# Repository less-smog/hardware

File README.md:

# IMPORTANT NOTE

The current revision (rev2) is undergoing tests - it's best to wait until the hardware has been well-tested before ordering PCBs and such.

# Open Hardware Air Pollution sensor

## housing
KRADEX Z56JPH housing is selected. Drawings and  3D models are available at [manufacturers site](https://www.kradex.com.pl/shop?product=z56).

## 3D model
Models from KiCad 4.0.7 release are used where available. Other models are in \lib\packages3d\ directory. You must copy them to KiCad KISYS3DMOD directory (i.e. C:\Program Files\KiCad\share\kicad\modules\packages3d on Windows). These models are:

* ESP-12E by [Jerry Dunmire (jdunmire)](https://github.com/jdunmire/kicad-ESP8266) (under Creative Commons Attribution-ShareAlike 4.0 International License)
* Molex 530470810, 530480810, 1050170001 by [Molex](https://www.molex.com/)
* MicroswitchSmd_4.3 by [Würth Elektronik](http://katalog.we-online.com/en/em/TASV_6X6_SMD?sid=3e9e02d6c0)
* Other are custom made

## LICENSE

This design has been released under the CERN Open Hardware Licence v1.2. We require that you notify us when you undertake either mass-production
of this design, or incorporate this design into an existing product, by e-mailing us at product@less-smog.org

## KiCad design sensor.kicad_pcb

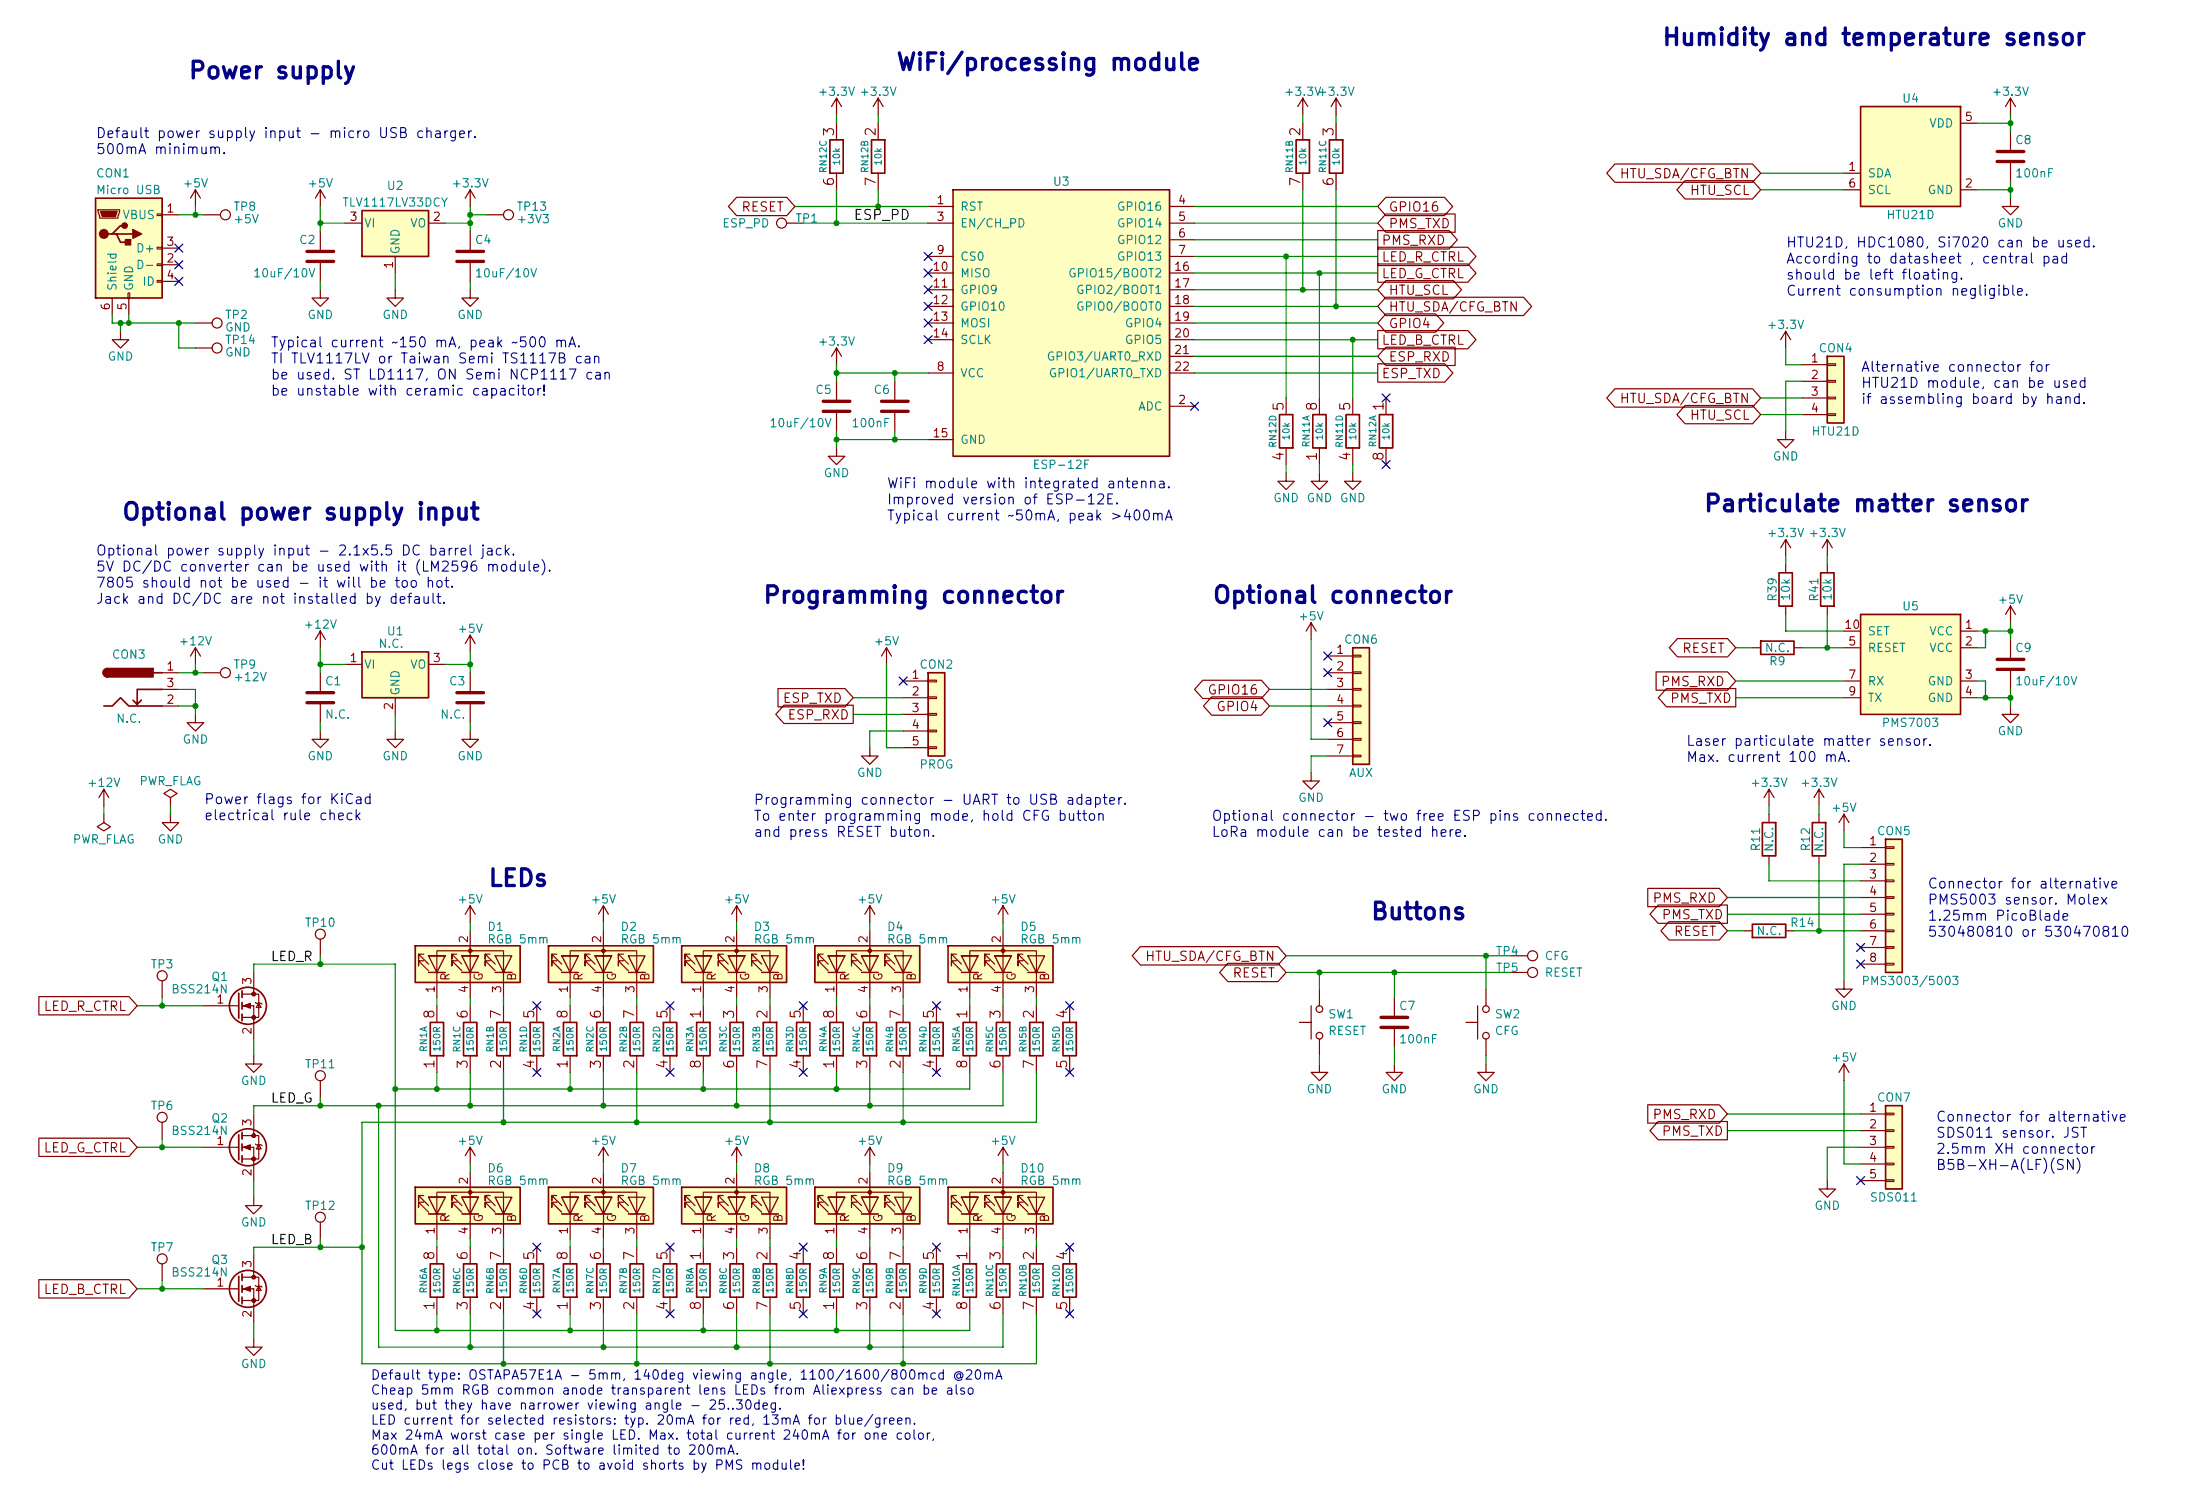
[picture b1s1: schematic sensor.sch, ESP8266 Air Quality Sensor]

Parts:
C1, C3: N.C.; 0805_M
C2, C4, C5, C9: 10uF/10V; 0805_M
C6, C7, C8: 100nF; 0603_M
CON1: Micro USB; USB_Micro-B_Molex-105017-0001
CON2: PROG; Pin_Header_Straight_1x05_Pitch2.54mm
CON3: N.C.; BARREL_JACK
CON4: HTU21D; HTU21D_module
CON5: PMS3003/5003; Molex_PicoBlade_53048-0810
CON6: AUX; E45-TTL-1W
CON7: SDS011; B5B-XH-A(LF)(SN)
D1, D2, D3, D4, D5, D6, D7, D8, D9, D10: RGB 5mm; LED_D5.0mm-4
Q1, Q2, Q3: BSS214N; SOT-23
R9, R11, R12, R14: N.C.; 0603_R_M
R39, R41: 10k; 0603_R_M
RN1, RN2, RN3, RN4, RN5, RN6, RN7, RN8, RN9, RN10: 150R; 4x0603_M
RN11, RN12: 10k; 4x0603_M
SW1: RESET; MicroswitchSmd-4.3_N
SW2: CFG; MicroswitchSmd-4.3_N
TP1: ESP_PD; TP_1.0_0.5_THT
TP2, TP14: GND; TP_1.7_1.0_THT
TP3, TP6, TP7, TP10, TP11, TP12: -; TP_1.0_0.5_THT
TP4: CFG; TP_1.7_1.0_THT
TP5: RESET; TP_1.7_1.0_THT
TP8: +5V; TP_1.0_0.5_THT
TP9: +12V; TP_1.0_0.5_THT
TP13: +3V3; TP_1.0_0.5_THT
U1: N.C.; 5V_DC_DC
U2: TLV1117LV33DCY; SOT-223-3Lead_TabPin2
U3: ESP-12F
U4: HTU21D
U5: PMS7003; PMS7003_THT

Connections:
+3V3: C4.1, C5.1, C6.1, C8.1, CON4.1, R11.2, R12.2, R39.1, R41.1, RN11.2 (1), RN11.3 (1), RN12.2 (1), RN12.3 (1), TP13.1, U2.2 (VO), U3.8 (VCC), U4.5 (VDD)
+5V: C2.1, C3.1, C9.1, CON1.1 (VBUS), CON2.5, CON5.1, CON6.6, CON7.4, D1.2 (A), D2.2 (A), D3.2 (A), D4.2 (A), D5.2 (A), D6.2 (A), D7.2 (A), D8.2 (A), D9.2 (A), D10.2 (A), TP8.1, U1.3 (VO), U2.3 (VI), U5.1 (VCC), U5.2 (VCC)
+12V: C1.1, CON3.1, TP9.1, U1.1 (VI)
/ESP_PD: RN12.6 (2), TP1.1, U3.3 (EN/CH_PD)
/LED_B: Q3.3 (D), RN1.2 (1), RN2.2 (1), RN3.7 (2), RN4.2 (1), RN5.7 (2), RN6.2 (1), RN7.2 (1), RN8.7 (2), RN9.2 (1), RN10.7 (2), TP12.1
/LED_G: Q2.3 (D), RN1.3 (1), RN2.3 (1), RN3.6 (2), RN4.3 (1), RN5.6 (2), RN6.3 (1), RN7.3 (1), RN8.6 (2), RN9.3 (1), RN10.6 (2), TP11.1
/LED_R: Q1.3 (D), RN1.1, RN2.1, RN3.8 (2), RN4.1, RN5.8 (2), RN6.1, RN7.1, RN8.8 (2), RN9.1, RN10.8 (2), TP10.1
ESP_RXD: CON2.3, U3.21 (GPIO3/UART0_RXD)
ESP_TXD: CON2.2, U3.22 (GPIO1/UART0_TXD)
GND: C1.2, C2.2, C3.2, C4.2, C5.2, C6.2, C7.2, C8.2, C9.2, CON1.5 (GND), CON1.6 (Shield), CON2.4, CON3.2, CON3.3, CON4.2, CON5.2, CON6.7, CON7.3, Q1.2 (S), Q2.2 (S), Q3.2 (S), RN11.1, RN11.4 (1), RN12.4 (1), SW1.2, SW2.2, TP2.1, TP14.1, U1.2 (GND), U2.1 (GND), U3.15 (GND), U4.2 (GND), U5.3 (GND), U5.4 (GND)
GPIO4: CON6.4, U3.19 (GPIO4)
GPIO16: CON6.3, U3.4 (GPIO16)
HTU_SCL: CON4.4, RN11.7 (2), U3.17 (GPIO2/BOOT1), U4.6 (SCL)
HTU_SDA/CFG_BTN: CON4.3, RN11.6 (2), SW2.1, TP4.1, U3.18 (GPIO0/BOOT0), U4.1 (SDA)
LED_B_CTRL: Q3.1 (G), RN11.5 (2), TP7.1, U3.20 (GPIO5)
LED_G_CTRL: Q2.1 (G), RN11.8 (2), TP6.1, U3.16 (GPIO15/BOOT2)
LED_R_CTRL: Q1.1 (G), RN12.5 (2), TP3.1, U3.7 (GPIO13)
unnamed: CON5.3, R11.1
unnamed: CON5.6, R12.1, R14.1
unnamed: D1.1 (RK), RN1.8 (2)
unnamed: D1.3 (BK), RN1.7 (2)
unnamed: D1.4 (GK), RN1.6 (2)
unnamed: D2.1 (RK), RN2.8 (2)
unnamed: D2.3 (BK), RN2.7 (2)
unnamed: D2.4 (GK), RN2.6 (2)
unnamed: D3.1 (RK), RN3.1
unnamed: D3.3 (BK), RN3.2 (1)
unnamed: D3.4 (GK), RN3.3 (1)
unnamed: D4.1 (RK), RN4.8 (2)
unnamed: D4.3 (BK), RN4.7 (2)
unnamed: D4.4 (GK), RN4.6 (2)
unnamed: D5.1 (RK), RN5.1
unnamed: D5.3 (BK), RN5.2 (1)
unnamed: D5.4 (GK), RN5.3 (1)
unnamed: D6.1 (RK), RN6.8 (2)
unnamed: D6.3 (BK), RN6.7 (2)
unnamed: D6.4 (GK), RN6.6 (2)
unnamed: D7.1 (RK), RN7.8 (2)
unnamed: D7.3 (BK), RN7.7 (2)
unnamed: D7.4 (GK), RN7.6 (2)
unnamed: D8.1 (RK), RN8.1
unnamed: D8.3 (BK), RN8.2 (1)
unnamed: D8.4 (GK), RN8.3 (1)
unnamed: D9.1 (RK), RN9.8 (2)
unnamed: D9.3 (BK), RN9.7 (2)
unnamed: D9.4 (GK), RN9.6 (2)
unnamed: D10.1 (RK), RN10.1
unnamed: D10.3 (BK), RN10.2 (1)
unnamed: D10.4 (GK), RN10.3 (1)
unnamed: R39.2, U5.10 (SET)
unnamed: R9.1, R41.2, U5.5 (RESET)
PMS_RXD: CON5.4, CON7.1, U3.6 (GPIO12), U5.7 (RX)
PMS_TXD: CON5.5, CON7.2, U3.5 (GPIO14), U5.9 (TX)
RESET: C7.1, R9.2, R14.2, RN12.7 (2), SW1.1, TP5.1, U3.1 (RST)

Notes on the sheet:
WiFi module with integrated antenna. Improved version of ESP-12E. Typical current ~~50mA, peak >400mA
HTU21D, HDC1080, Si7020 can be used. According to datasheet , central pad should be left floating. Current consumption negligible.
Laser particulate matter sensor. Max. current 100 mA.
Default type: OSTAPA57E1A - 5mm, 140deg viewing angle, 1100/1600/800mcd @20mA Cheap 5mm RGB common anode transparent lens LEDs from Aliexpress can be also used, but they have narrower viewing angle - 25..30deg. LED current for selected resistors: typ. 20mA for red, 13mA for blue/green. Max 24mA wor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
Typical current ~~150 mA, peak ~~500 mA. TI TLV1117LV or Taiwan Semi TS1117B can be used. ST LD1117, ON Semi NCP1117 can be unstable with ceramic capacitor!
Optional power supply input - 2.1x5.5 DC barrel jack. 5V DC/DC converter can be used with it (LM2596 module). 7805 should not be used - it will be too hot. Jack and DC/DC are not installed by default.
Default power supply input - micro USB charger. 500mA minimum.
Programming connector - UART to USB adapter. To enter programming mode, hold CFG button and press RESET buton.
Alternative connector for HTU21D module, can be used if assembling board by hand.
Humidity and temperature sensor
Particulate matter sensor
Connector for alternative PMS5003 sensor. Molex 1.25mm PicoBlade 530480810 or 530470810
Buttons
LEDs
WiFi/processing module
Programming connector
Power supply
Optional power supply input
Power flags for KiCad electrical rule check
Optional connector
Optional connector - two free ESP pins connected. LoRa module can be tested here.
Connector for alternative SDS011 sensor. JST 2.5mm XH connector B5B-XH-A(LF)(SN)

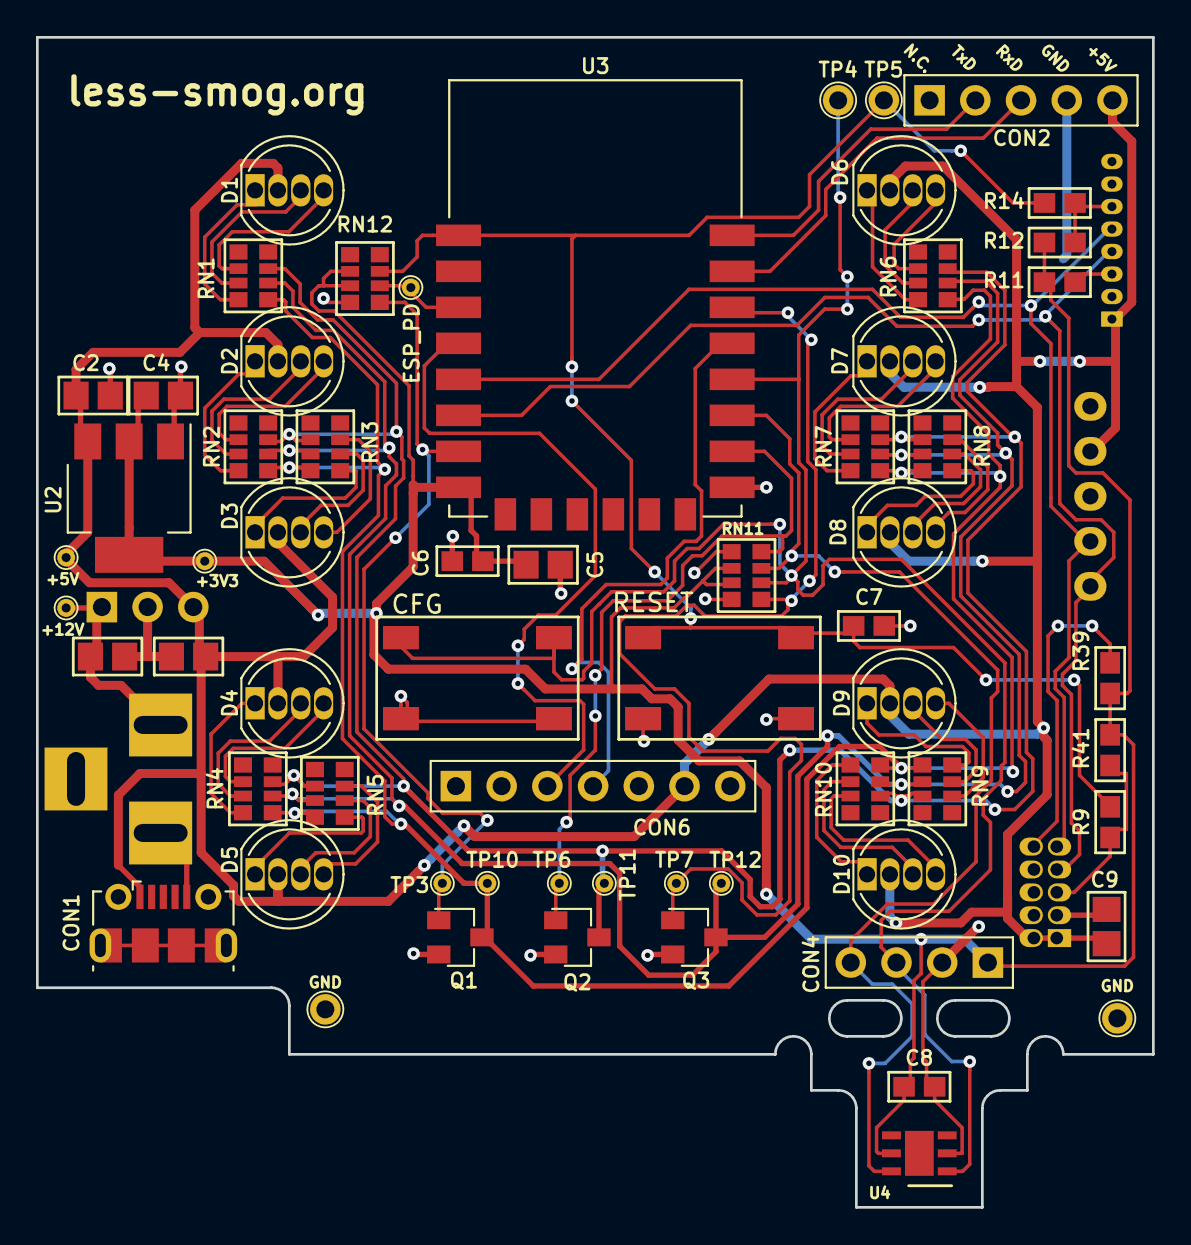
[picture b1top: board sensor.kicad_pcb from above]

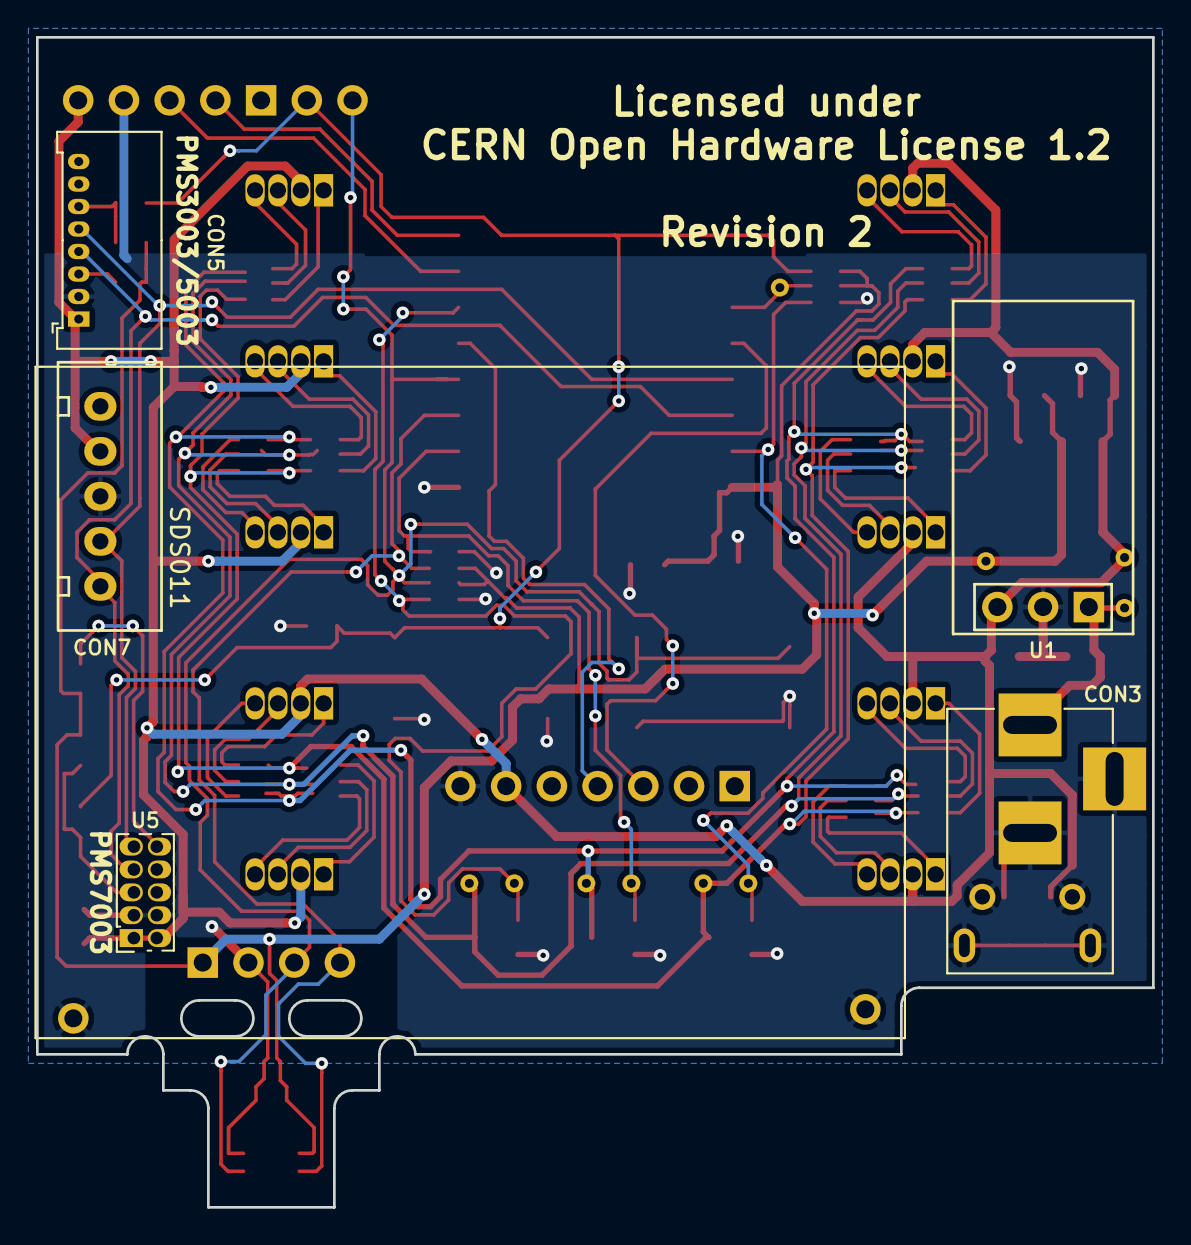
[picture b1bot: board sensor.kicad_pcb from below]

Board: 2 copper layers, 62.0 x 65.0 mm, 68 parts (5 on the bottom side), 54 nets.

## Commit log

2018-02-17 Initial commit of KiCad libraries
2018-02-17 Initial commit of schematic and PCB
2018-02-18 Use libraries from KiCad 4.0.7 instead of new from KiCad GitHub.
2018-02-18 Working on connections
2018-02-18 Add power supplies and other connections.
2018-02-20 Change packages to bigger ones, simpler to assemble.
2018-02-20 Schematic finishing and cleanup.
2018-02-20 Fix ERC errors, add more testpoints.
2018-02-21 Initial draft PCB placement
2018-02-21 Change some footprint pads to bigger ones.
2018-02-23 Add HTU21D module footprint
2018-02-23 Routing in progress
2018-02-24 Routed PCB, routing to be optimized
2018-02-24 Change some footprints. Optimize routing.
2018-02-24 Add 3D models
2018-02-24 Update 3D model
2018-02-24 Update PDF schematic
2018-02-25 Clean-up silkscreen.
2018-02-26 Update 3D model.
2018-03-06 TODO
2018-03-08 Added licensing information, Open Hardware logo, project URL, etc.
2018-03-08 Added LICENSE, PRODUCT contact information.
2018-03-10 Made a few layers visible.
2018-03-10 Generated gerbers for manufacturing.
2018-03-10 Added 1 click bom.
2018-03-10 Added BOM.
2018-03-10 Added kitspace.yaml
2018-03-11 Remove old gerber files
2018-03-11 Update PCB to for production: - change via drills to 0.3mm - update solder mask expansion - update paste mask expansion - generate gerber files
2018-03-11 Add board and stencil dimensions
2018-03-14 Update soldermask color for kitspace preview
2018-03-14 Clean BOM
2018-03-14 Update BOM: remove unneded connector, add TME column, remove Farnell RL endings
2018-03-14 Added missing TME part.
2018-05-06 Update assembly drawing and generate pdf. Fix alternative Q4..Q6 values.
2018-05-12 Added a note, clarified licensing terms.
2018-05-20 [#4] Change LEDs to 5mm THT on schematic.
2018-05-20 [#4] Change LEDs to 5mm THT on schematic. [#8] Remove bigger transistor packages from schematic
2018-05-20 [#2] Change LED resistors to chip arrays.
2018-05-20 Change ESP connections. [#6] Free hardware SPI for Lora module [#9] Disconnect PMS_SET and PMS_RESET Other connections are also moved. ESP programming serial port merged with PMS serial.
2018-05-21 Go back to previous ESP pinout, except I2C and LED_B_CTRL [#6] Hardware SPI for Lora module not available.
2018-05-21 [#5] Reduce solder paste on micro USB connector pads
2018-05-21 Change components to smaller ones. [#2] Change resistors to chip arrays.
2018-05-21 Add library packages
2018-05-21 [#3] Change optional 7805 to DC/DC
2018-05-21 Fix ERC errors
2018-05-22 Crudely routed board. Changed some footprints to easier to solder.
2018-05-22 Routing optimization
2018-05-22 Button position correction
2018-05-22 PDF schematic added
2018-05-23 Add connector for SDS011 Close #10
2018-05-23 [#10] Update schematic PDF. Add remaining library footprints.
2018-05-23 Update silkscreen
2018-05-23 Update Gerber files
2018-05-24 Updated 1 click BOM.
2018-05-24 Updated README.
2018-06-23 Sorted component references for easier assembly.

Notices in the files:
sensor.kicad_pcb:
Licensed under
CERN Open Hardware License 1.2
